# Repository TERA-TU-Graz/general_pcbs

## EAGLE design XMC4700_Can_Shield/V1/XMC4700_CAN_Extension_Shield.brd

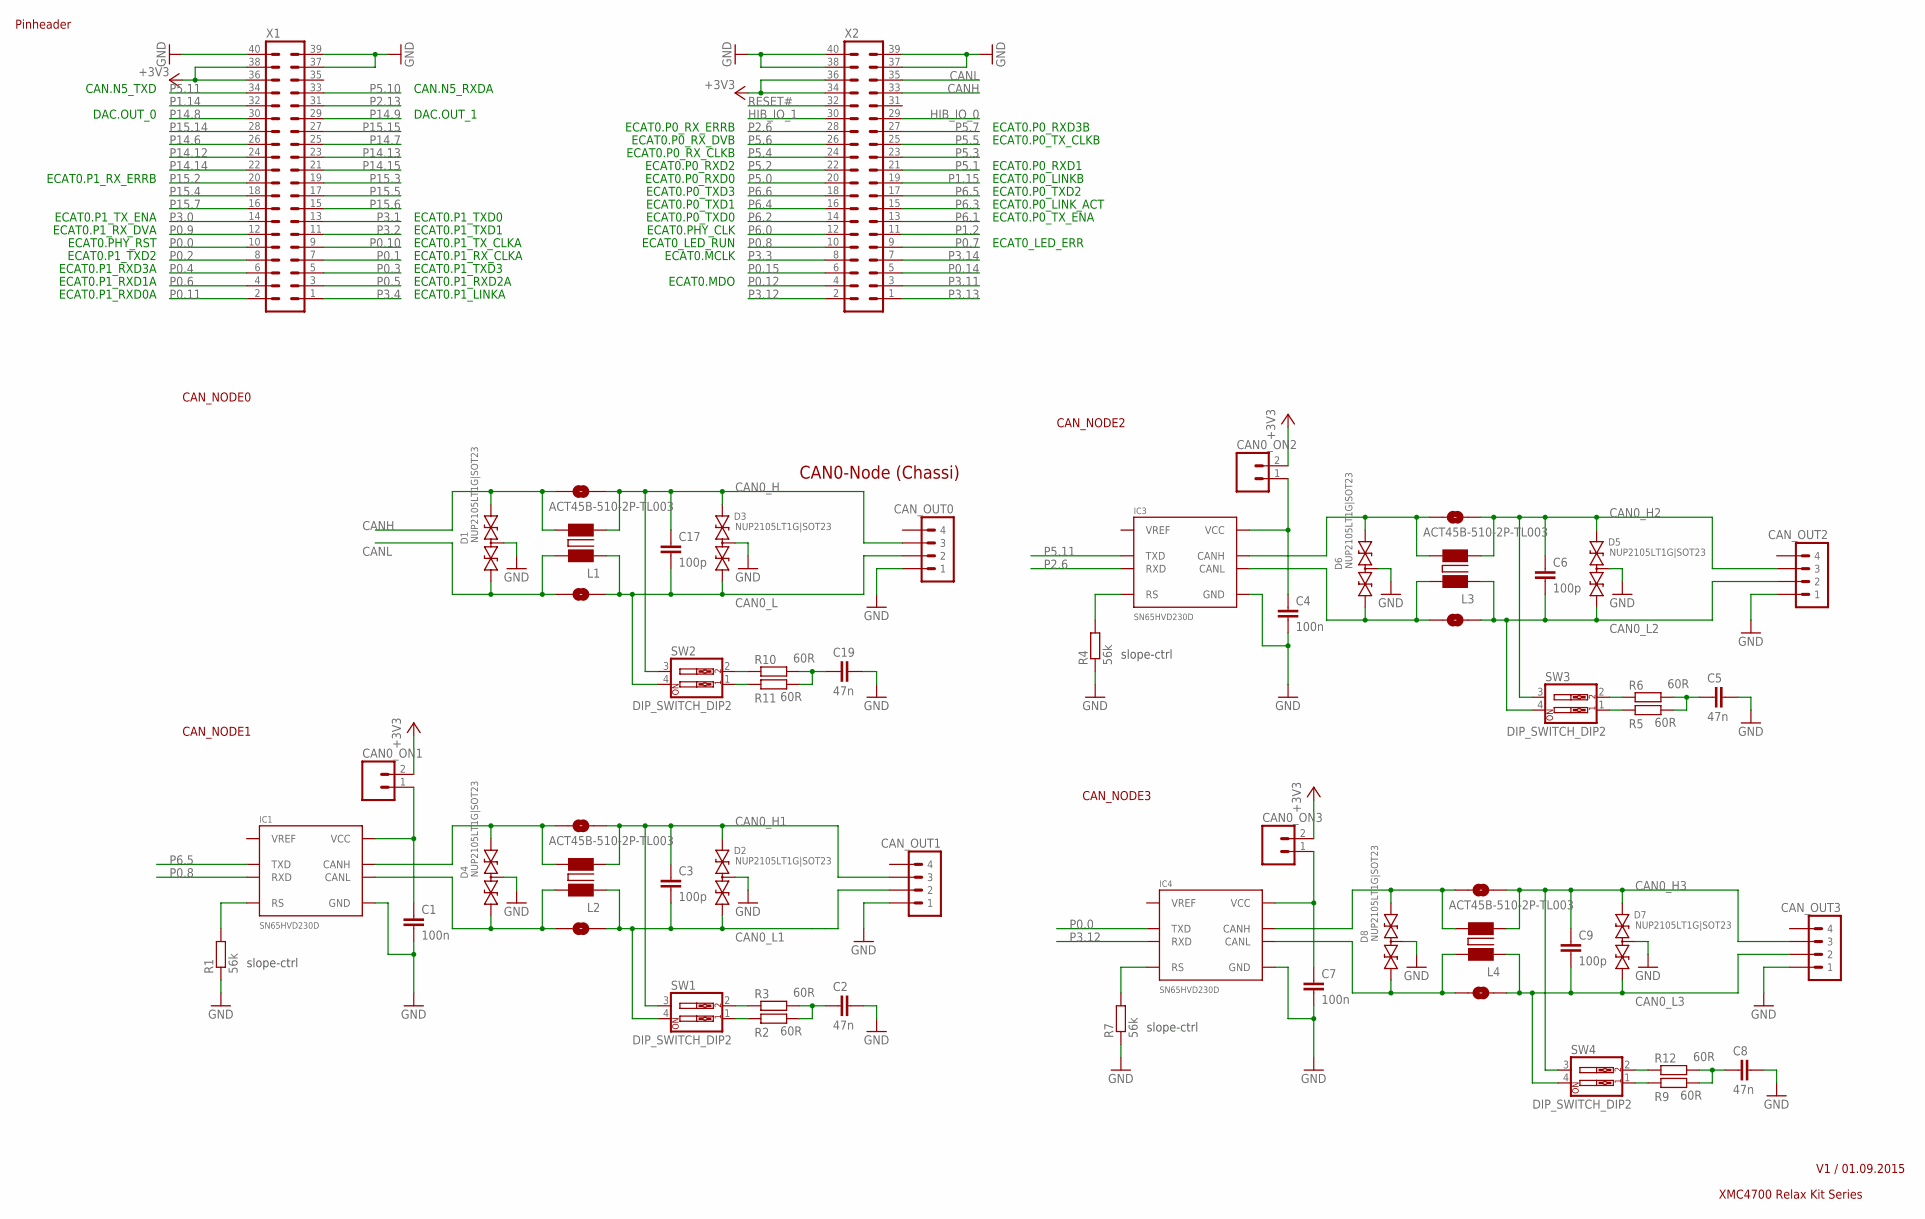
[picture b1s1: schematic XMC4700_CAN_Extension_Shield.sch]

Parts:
C1, C4, C7: 100n; C0805
C2, C5, C8, C19: 47n; C0805
C3, C6, C9, C17: 100p; C0805
CAN0_ON1, CAN0_ON2, CAN0_ON3: M02PAD; 1X02
CAN_OUT0, CAN_OUT1, CAN_OUT2, CAN_OUT3: CIOC_4-1-FV-A; CIOC_4-1-FV
D1, D2, D3, D4, D5, D6, D7, D8: NUP2105LT1G|SOT23; SOT23
IC1, IC3, IC4: SN65HVD230D; SO08
L1, L2, L3, L4: ACT45B-510-2P-TL003; ACT45B
R1, R4, R7: 56k; R0805
R2, R3, R5, R6, R9, R10, R11, R12: 60R; R0805
SJ1, SJ2, SJ3, SJ4, SJ5, SJ6, SJ7, SJ8: SOLDERJUMPERNO; SJ_2S-NO
SW1, SW2, SW3, SW4: DIP_SWITCH_DIP2; DIPSWITCH-02
X1, X2: MA20-2

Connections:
+3V3: CAN0_ON1.2, CAN0_ON2.2, CAN0_ON3.2, X1.36, X1.38, X2.34, X2.36
CAN0_H: C17.1, CAN_OUT0.3, D3.2, L1.P$1 (1), SJ1.2, SW2.3
CAN0_H1: C3.1, CAN_OUT1.3, D2.2, L2.P$1 (1), SJ3.2, SW1.3
CAN0_H2: C6.1, CAN_OUT2.3, D5.2, L3.P$1 (1), SJ5.2, SW3.3
CAN0_H3: C9.1, CAN_OUT3.3, D7.2, L4.P$1 (1), SJ7.2, SW4.3
CAN0_L: C17.2, CAN_OUT0.2, D3.1, L1.P$3 (3), SJ2.2, SW2.4
CAN0_L1: C3.2, CAN_OUT1.2, D2.1, L2.P$3 (3), SJ4.2, SW1.4
CAN0_L2: C6.2, CAN_OUT2.2, D5.1, L3.P$3 (3), SJ6.2, SW3.4
CAN0_L3: C9.2, CAN_OUT3.2, D7.1, L4.P$3 (3), SJ8.2, SW4.4
CANH: D1.2, L1.P$2 (2), SJ1.1, X2.33
CANL: D1.1, L1.P$4 (4), SJ2.1, X2.35
GND: C1.2, C2.2, C4.2, C5.2, C7.2, C8.2, C19.2, CAN_OUT0.1, CAN_OUT1.1, CAN_OUT2.1, CAN_OUT3.1, D1.3, D2.3, D3.3, D4.3, D5.3, D6.3, D7.3, D8.3, IC1.2 (GND), IC3.2 (GND), IC4.2 (GND), R1.1, R4.1, R7.1, X1.37, X1.39, X1.40, X2.37, X2.38, X2.39, X2.40
HIB_IO_0: X2.29
HIB_IO_1: X2.30
unnamed: IC1.8 (RS), R1.2
unnamed: C1.1, CAN0_ON1.1, IC1.3 (VCC)
unnamed: C2.1, R2.2, R3.2
unnamed: D4.2, IC1.7 (CANH), L2.P$2 (2), SJ3.1
unnamed: R10.1, SW2.2
unnamed: D4.1, IC1.6 (CANL), L2.P$4 (4), SJ4.1
unnamed: R2.1, SW1.1
unnamed: R3.1, SW1.2
unnamed: IC3.8 (RS), R4.2
unnamed: C4.1, CAN0_ON2.1, IC3.3 (VCC)
unnamed: C5.1, R5.2, R6.2
unnamed: D6.2, IC3.7 (CANH), L3.P$2 (2), SJ5.1
unnamed: D6.1, IC3.6 (CANL), L3.P$4 (4), SJ6.1
unnamed: R5.1, SW3.1
unnamed: R11.1, SW2.1
unnamed: C19.1, R10.2, R11.2
unnamed: R6.1, SW3.2
unnamed: IC4.8 (RS), R7.2
unnamed: C7.1, CAN0_ON3.1, IC4.3 (VCC)
unnamed: C8.1, R9.2, R12.2
unnamed: D8.2, IC4.7 (CANH), L4.P$2 (2), SJ7.1
unnamed: D8.1, IC4.6 (CANL), L4.P$4 (4), SJ8.1
unnamed: R9.1, SW4.1
unnamed: R12.1, SW4.2
P0.0: IC4.1 (TXD), X1.10
P0.1: X1.7
P0.2: X1.8
P0.3: X1.5
P0.4: X1.6
P0.5: X1.3
P0.6: X1.4
P0.7: X2.9
P0.8: IC1.4 (RXD), X2.10
P0.9: X1.12
P0.10: X1.9
P0.11: X1.2
P0.12: X2.4
P0.14: X2.5
P0.15: X2.6
P1.2: X2.11
P1.14: X1.32
P1.15: X2.19
P2.6: IC3.4 (RXD), X2.28
P2.13: X1.31
P3.0: X1.14
P3.1: X1.13
P3.2: X1.11
P3.3: X2.8
P3.4: X1.1
P3.11: X2.3
P3.12: IC4.4 (RXD), X2.2
P3.13: X2.1
P3.14: X2.7
P5.0: X2.20
P5.1: X2.21
P5.2: X2.22
P5.3: X2.23
P5.4: X2.24
P5.5: X2.25
P5.6: X2.26
P5.7: X2.27
P5.10: X1.33
P5.11: IC3.1 (TXD), X1.34
P6.0: X2.12
P6.1: X2.13
P6.2: X2.14
P6.3: X2.15
P6.4: X2.16
P6.5: IC1.1 (TXD), X2.17
P6.6: X2.18
P14.6: X1.26
P14.7: X1.25
P14.8: X1.30
P14.9: X1.29
P14.12: X1.24
P14.13: X1.23
P14.14: X1.22
P14.15: X1.21
P15.2: X1.20
P15.3: X1.19
P15.4: X1.18
P15.5: X1.17
P15.6: X1.15
P15.7: X1.16
P15.14: X1.28
P15.15: X1.27
RESET#: X2.32

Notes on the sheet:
Pinheader
ECAT0.MDO
ECAT0.P1_RXD0A
ECAT0.P1_TX_CLKA
ECAT0.P1_RX_DVA
ECAT0_LED_RUN
ECAT0_LED_ERR
ECAT0.P1_RXD1A
ECAT0.P1_RXD2A
ECAT0.P1_RXD3A
ECAT0.P1_TXD3
ECAT0.P1_TXD2
ECAT0.P1_RX_CLKA
ECAT0.PHY_RST
ECAT0.P0_LINKB
ECAT0.P0_TXD3
ECAT0.P0_TXD2
ECAT0.P0_TXD1
ECAT0.P0_LINK_ACT
ECAT0.P0_TXD0
ECAT0.P0_TX_ENA
ECAT0.PHY_CLK
ECAT0.P1_RX_ERRB
ECAT0.P0_RXD3B
ECAT0.P0_RX_DVB
ECAT0.P0_TX_CLKB
ECAT0.P0_RX_CLKB
ECAT0.P0_RXD2
ECAT0.P0_RXD1
ECAT0.P0_RXD0
ECAT0.P1_LINKA
ECAT0.MCLK
ECAT0.P1_TXD1
ECAT0.P1_TXD0
ECAT0.P1_TX_ENA
ECAT0.P0_RX_ERRB
DAC.OUT_0
DAC.OUT_1
CAN.N5_TXD
CAN.N5_RXDA

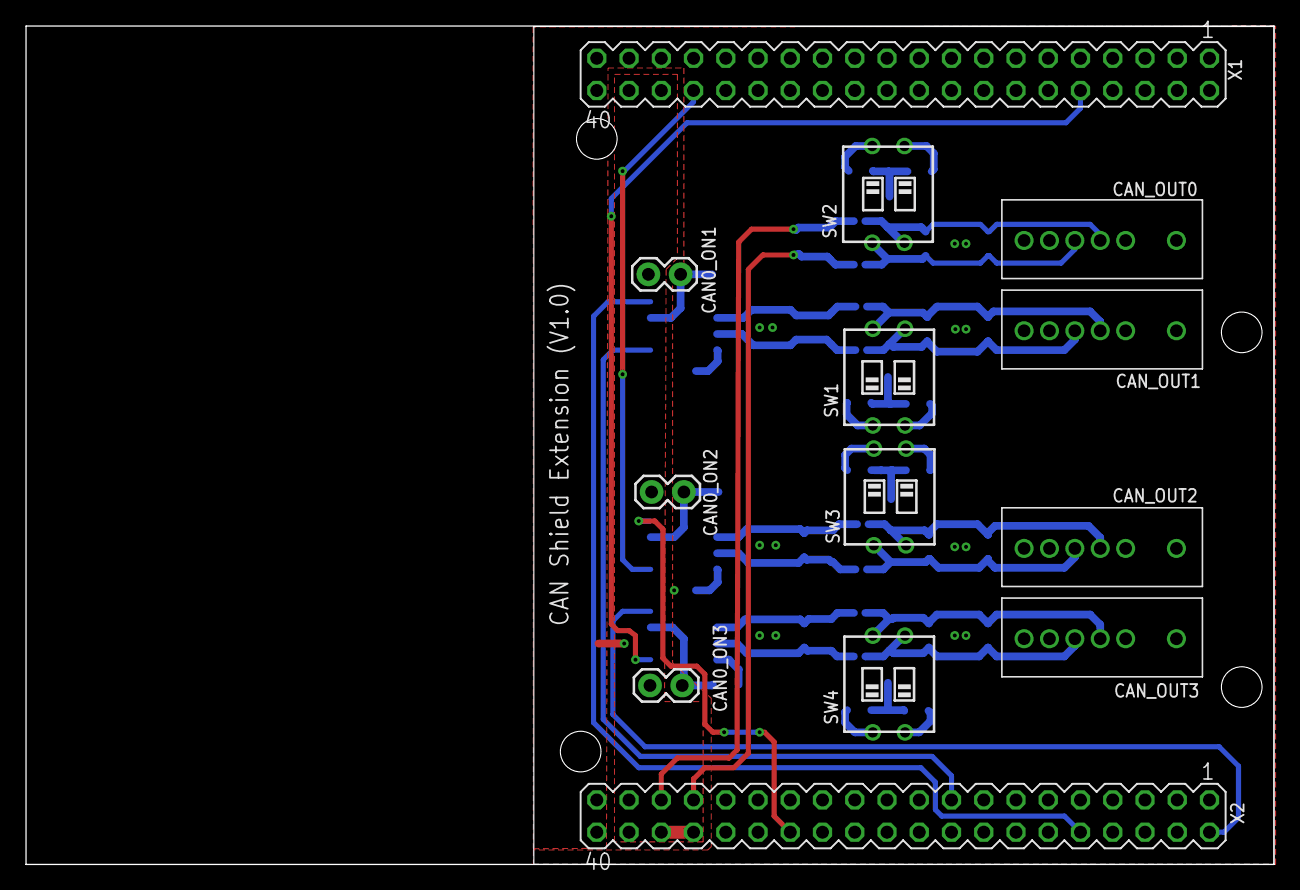
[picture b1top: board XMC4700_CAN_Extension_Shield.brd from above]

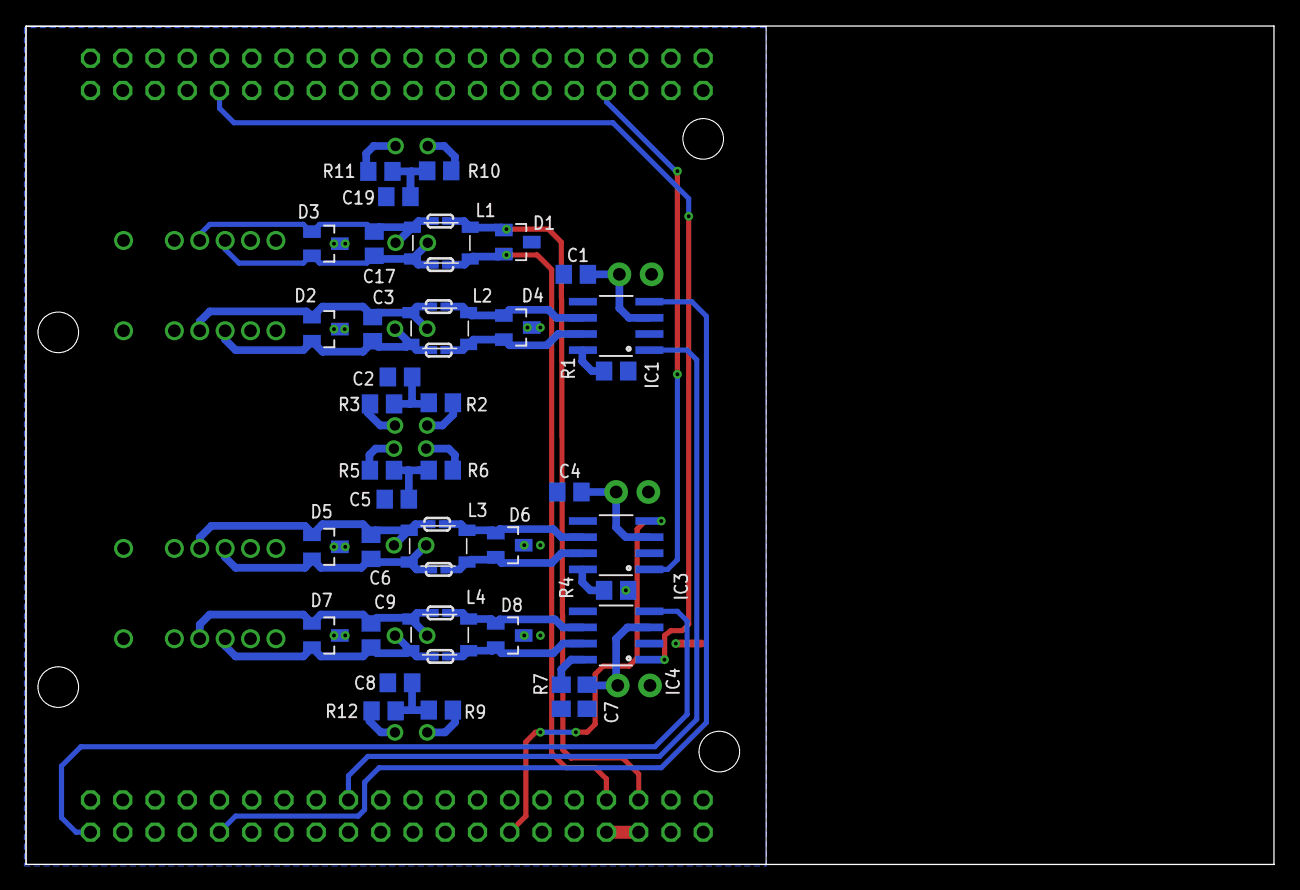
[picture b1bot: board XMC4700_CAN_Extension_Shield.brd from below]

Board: 4 copper layers, 98.3 x 66.0 mm, 58 parts (45 on the bottom side), 42 nets.

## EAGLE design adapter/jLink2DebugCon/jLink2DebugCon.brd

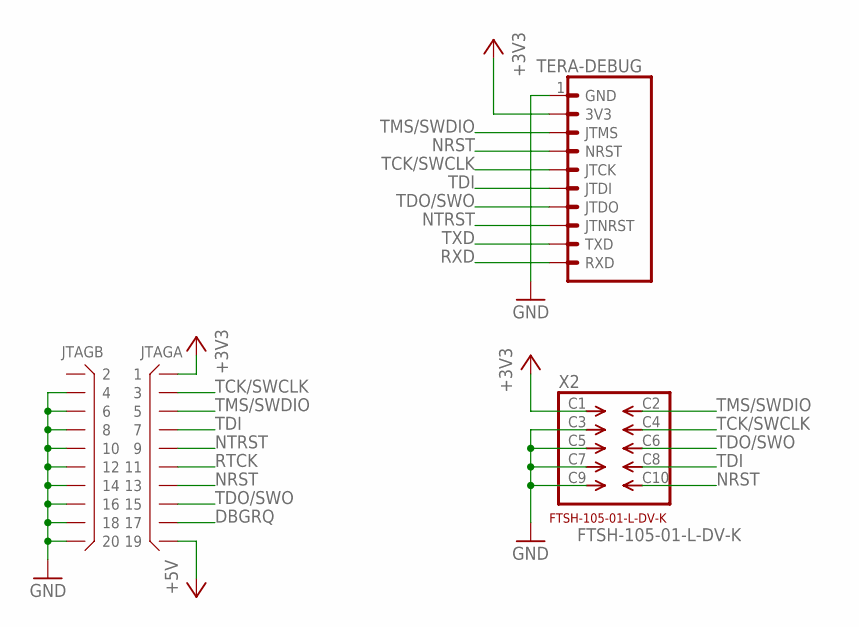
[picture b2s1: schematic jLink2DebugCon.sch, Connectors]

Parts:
JTAG: X10X2IR; X20R-IDC
TERA-DEBUG: TERA-PROG-DEBUG-10GERADE; 90130-1110
X2: FTSH-105-01-L-DV-K; SMD_10PIN_2ROW_1.27MM_SAMTEC

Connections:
+3V3: JTAG.1, TERA-DEBUG.2 (3V3), X2.C1
+5V: JTAG.19
DBGRQ: JTAG.17
GND: JTAG.4, JTAG.6, JTAG.8, JTAG.10, JTAG.12, JTAG.14, JTAG.16, JTAG.18, JTAG.20, TERA-DEBUG.1 (GND), X2.C3, X2.C5, X2.C7, X2.C9
NRST: JTAG.15, TERA-DEBUG.4 (NRST), X2.C10
NTRST: JTAG.3, TERA-DEBUG.8 (JTNRST)
RTCK: JTAG.11
RXD: TERA-DEBUG.10 (RXD)
TCK/SWCLK: JTAG.9, TERA-DEBUG.5 (JTCK), X2.C4
TDI: JTAG.5, TERA-DEBUG.6 (JTDI), X2.C8
TDO/SWO: JTAG.13, TERA-DEBUG.7 (JTDO), X2.C6
TMS/SWDIO: JTAG.7, TERA-DEBUG.3 (JTMS), X2.C2
TXD: TERA-DEBUG.9 (TXD)

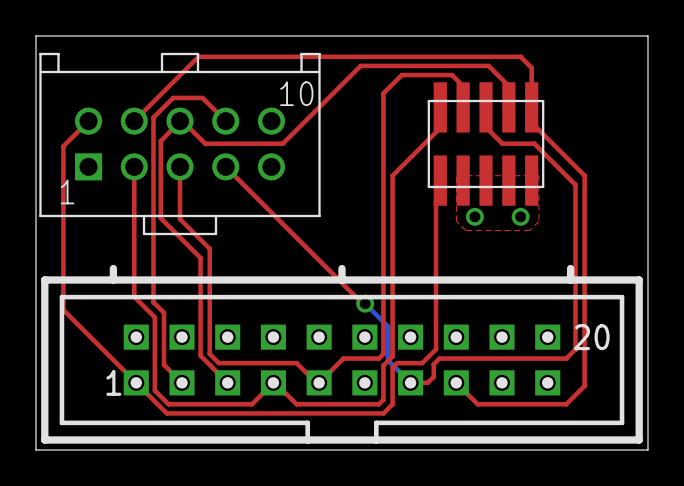
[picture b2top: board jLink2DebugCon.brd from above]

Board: 2 copper layers, 34.0 x 23.0 mm, 3 parts (0 on the bottom side), 8 nets.

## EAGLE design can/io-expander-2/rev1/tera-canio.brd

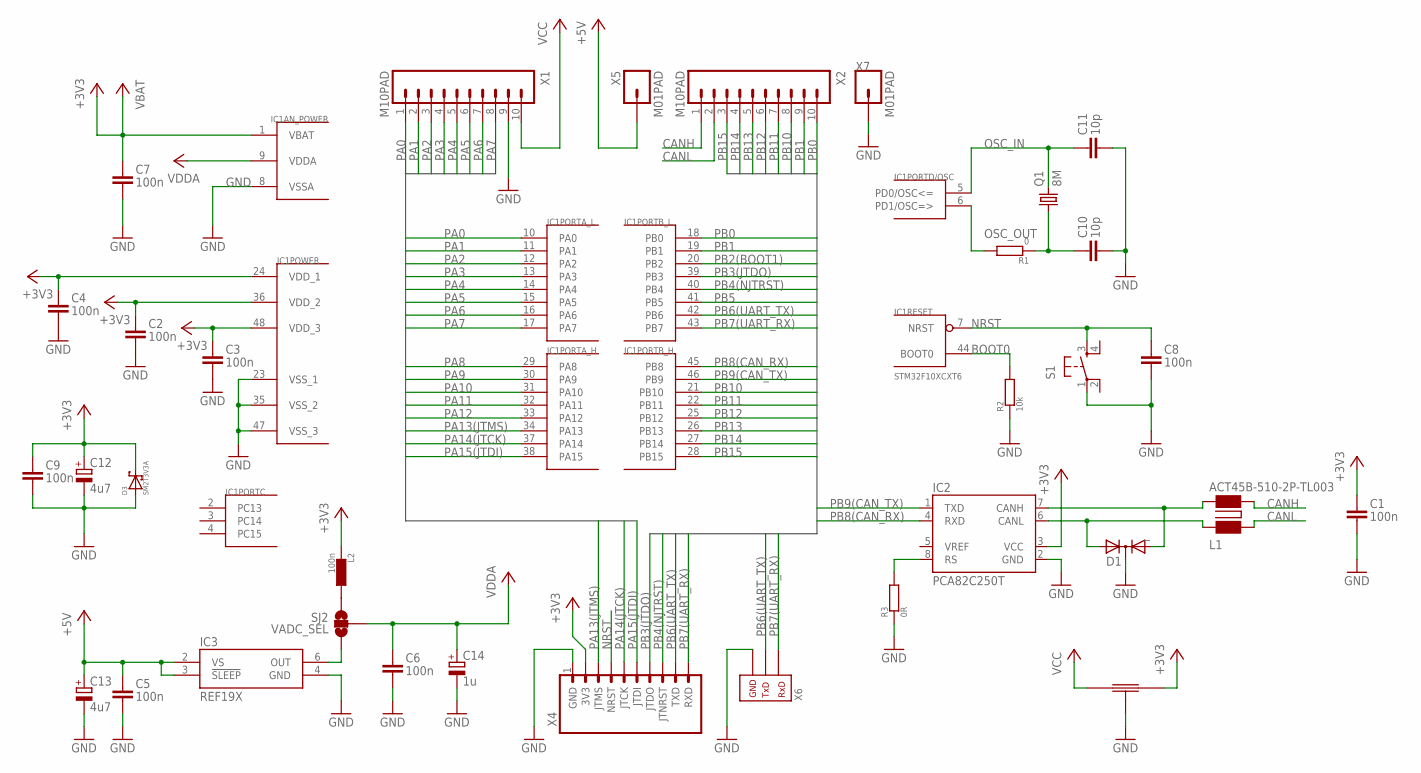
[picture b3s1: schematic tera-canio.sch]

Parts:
C1, C2, C3, C4, C5, C6, C7, C8, C9: 100n; C0805
C10, C11: 10p; C0805
C12, C13: 4u7; CT3528
C14: 1u; CT3216
C18: C-FILTER; C_FILTER
D1: _; SOT23
D3: SM2T3V3A
IC1: STM32F10XCXT6; TQFP48
IC2: PCA82C250T; SOIC-8
IC3: REF19X; SO08
L1: ACT45B-510-2P-TL003; ACT45B
L2: 100n; R0805
Q1: 8M; 0305
R1: 0; R0805
R2: 10k; R0805
R3: 0R; R0805
S1: TAC_SWITCH; FSMJSMA
SJ2: VADC_SEL; SJ_3_PASTE1&2
X1, X2: M10PAD; 1X10
X4: TERA-PROG-DEBUG-10GERADE; 90130-1110
X5, X7: M01PAD; 1X01
X6: RS232V; 6410-03

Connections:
+3V3: C1.2, C2.2, C3.2, C4.2, C7.2, C9.2, C12.+, C18.3 (OUT), D3.P$2, IC1.1 (VBAT), IC1.24 (VDD_1), IC1.36 (VDD_2), IC1.48 (VDD_3), IC2.3 (VCC), L2.1, X4.2 (3V3)
+5V: C5.2, C13.+, IC3.2 (VS), IC3.3 (!SLEEP), X5.1
ASDF2: D1.1 (A1), IC2.7 (CANH), L1.P$1 (1)
ASDF3: D1.2 (A2), IC2.6 (CANL), L1.P$3 (3)
BOOT0: IC1.44 (BOOT0), R2.2
CANH: L1.P$2 (2), X2.1
CANL: L1.P$4 (4), X2.2
GND: C1.1, C2.1, C3.1, C4.1, C5.1, C6.1, C7.1, C8.1, C9.1, C10.1, C11.1, C12.-, C13.-, C14.-, C18.2 (GND), D1.3 (C), D3.P$1, D3.P$11, IC1.8 (VSSA), IC1.23 (VSS_1), IC1.35 (VSS_2), IC1.47 (VSS_3), IC2.2 (GND), IC3.4 (GND), R2.1, R3.1, S1.1, X1.9, X4.1 (GND), X6.1 (GND), X7.1
GND1: C10.2, Q1.1, R1.1
unnamed: IC2.8 (RS), R3.2
unnamed: IC3.6 (OUT), SJ2.3
unnamed: L2.2, SJ2.1
NRST: C8.2, IC1.7 (NRST), S1.3, X4.4 (NRST)
OSC_IN: C11.2, IC1.5 (PD0/OSC<=), Q1.2
OSC_OUT: IC1.6 (PD1/OSC=>), R1.2
PA0: IC1.10 (PA0), X1.1
PA1: IC1.11 (PA1), X1.2
PA2: IC1.12 (PA2), X1.3
PA3: IC1.13 (PA3), X1.4
PA4: IC1.14 (PA4), X1.5
PA5: IC1.15 (PA5), X1.6
PA6: IC1.16 (PA6), X1.7
PA7: IC1.17 (PA7), X1.8
PA8: IC1.29 (PA8)
PA9: IC1.30 (PA9)
PA10: IC1.31 (PA10)
PA11: IC1.32 (PA11)
PA12: IC1.33 (PA12)
PA13(JTMS): IC1.34 (PA13), X4.3 (JTMS)
PA14(JTCK): IC1.37 (PA14), X4.5 (JTCK)
PA15(JTDI): IC1.38 (PA15), X4.6 (JTDI)
PB0: IC1.18 (PB0), X2.10
PB1: IC1.19 (PB1), X2.9
PB2(BOOT1): IC1.20 (PB2)
PB3(JTDO): IC1.39 (PB3), X4.7 (JTDO)
PB4(NJTRST): IC1.40 (PB4), X4.8 (JTNRST)
PB5: IC1.41 (PB5)
PB6(UART_TX): IC1.42 (PB6), X4.9 (TXD), X6.2 (TXD)
PB7(UART_RX): IC1.43 (PB7), X4.10 (RXD), X6.3 (RXD)
PB8(CAN_RX): IC1.45 (PB8), IC2.4 (RXD)
PB9(CAN_TX): IC1.46 (PB9), IC2.1 (TXD)
PB10: IC1.21 (PB10), X2.8
PB11: IC1.22 (PB11), X2.7
PB12: IC1.25 (PB12), X2.6
PB13: IC1.26 (PB13), X2.5
PB14: IC1.27 (PB14), X2.4
PB15: IC1.28 (PB15), X2.3
VCC: C18.1 (IN), X1.10
VDDA: C6.2, C14.+, IC1.9 (VDDA), SJ2.2

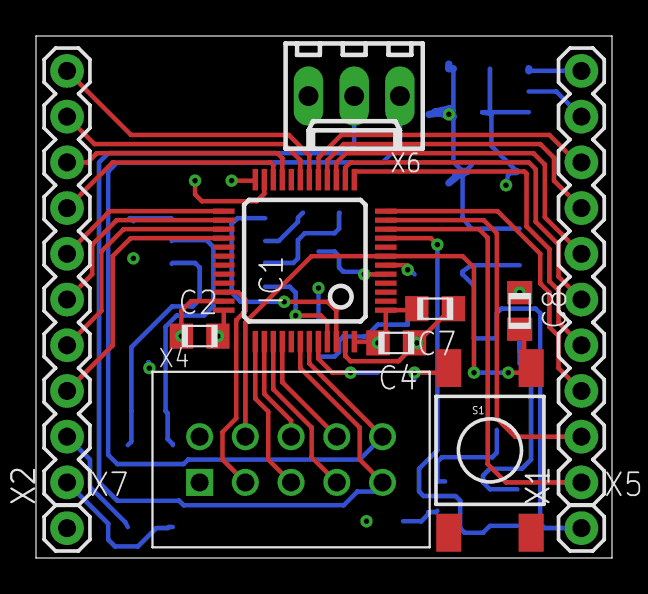
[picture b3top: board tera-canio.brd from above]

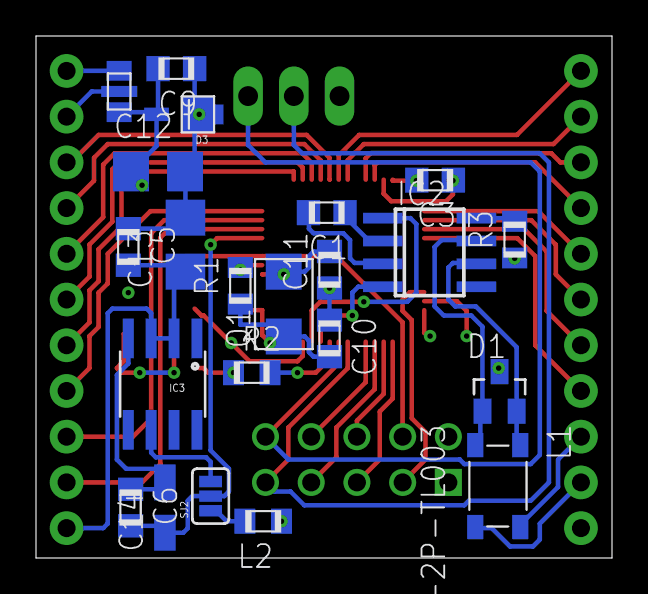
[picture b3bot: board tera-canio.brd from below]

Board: 4 copper layers, 32.0 x 29.0 mm, 34 parts (22 on the bottom side), 42 nets.

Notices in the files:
parts and their libraries:
SparkFun: Licensing: CC v3.0 Share-Alike You are welcome to use this library for commercial purposes.
